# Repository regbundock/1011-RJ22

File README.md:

# 1011 RJ22 CAB I/F & Terminators
This board is a development of the MERG CBUS RJ22 connector. It is the same size and the RJ22 sockets are positioned on the board exactly as the ones on the MERG board. It may similarly be sawn in half so that each half may be installed at opposite ends of the CAN bus. The differences lie firstly in the fact that there are four CAN bus interfaces rather than two which are all similarly orientated and secondly in the fact that the two 120 Ohm resistors may be routinely installed and individually connected to the CAN bus by applying a solder bridge to a jumper imprinted in the copper on the component side.

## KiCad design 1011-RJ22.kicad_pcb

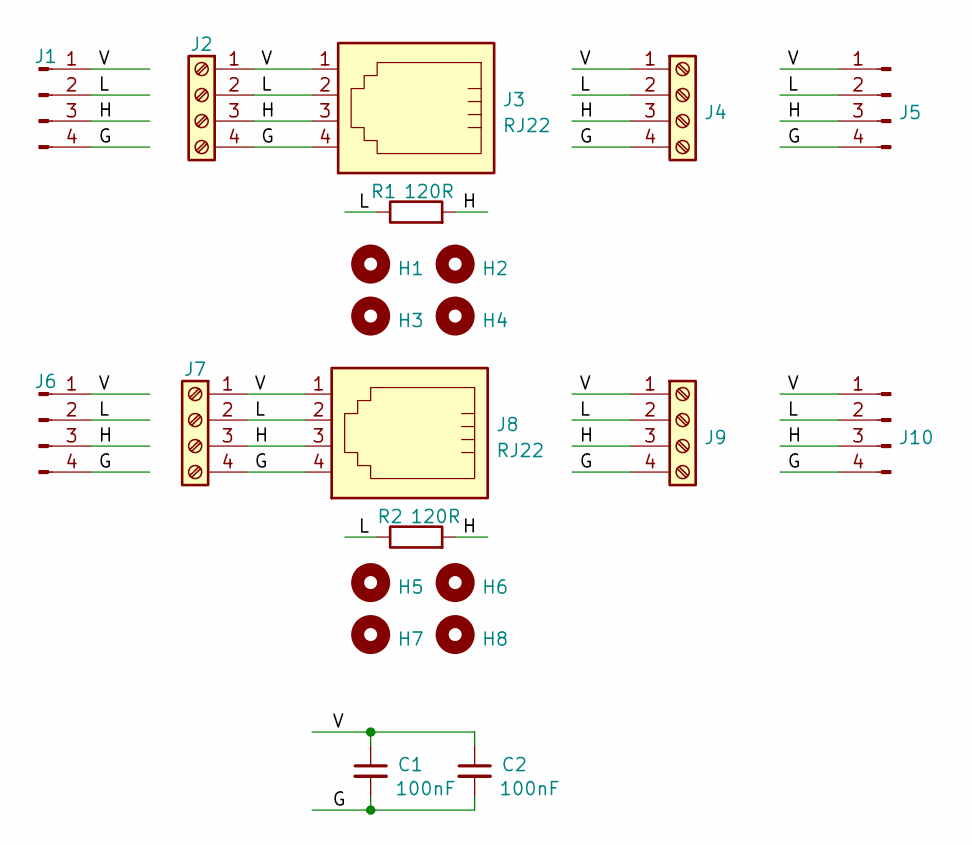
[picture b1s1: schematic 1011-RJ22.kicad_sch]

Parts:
C1, C2: 100nF; C_Disc_D5.0mm_W2.5mm_P5.00mm
H1, H2, H3, H4, H5, H6, H7, H8: MountingHole; MountingHole_3.2mm_M3_Pad
J1, J5, J6, J10: Conn_01x04_Male; PinHeader_1x04_P2.54mm_Vertical
J2, J4, J7, J9: Screw_Terminal_01x04; Camdenboss_3pt5mm_pitch_PCB_horizontal_4Way
J3, J8: RJ22
R1, R2: 120R; R_Axial_DIN0207_L6.3mm_D2.5mm_P10.16mm_Horizontal

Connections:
/G: C1.2, C2.2, J1.4, J2.4, J3.4, J4.4, J5.4, J6.4, J7.4, J8.4, J9.4, J10.4
/H: J1.3, J2.3, J3.3, J4.3, J5.3, J6.3, J7.3, J8.3, J9.3, J10.3, R1.2, R2.2
/L: J1.2, J2.2, J3.2, J4.2, J5.2, J6.2, J7.2, J8.2, J9.2, J10.2, R1.1, R2.1
/V: C1.1, C2.1, J1.1, J2.1, J3.1, J4.1, J5.1, J6.1, J7.1, J8.1, J9.1, J10.1

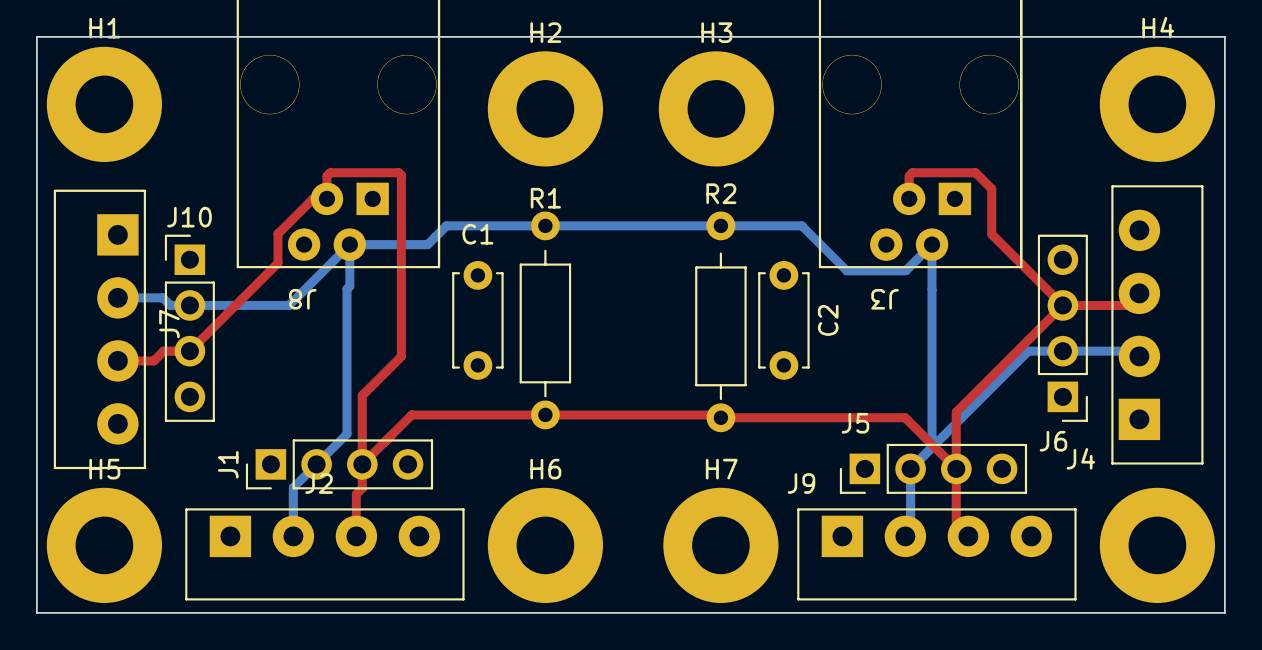
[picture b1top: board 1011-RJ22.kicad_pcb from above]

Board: 2 copper layers, 66.0 x 32.0 mm, 22 parts (0 on the bottom side), 4 nets.
